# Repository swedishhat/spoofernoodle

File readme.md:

This board is designed to act as an ISO7816 smart card emulator
as well as a pass-through for the card.

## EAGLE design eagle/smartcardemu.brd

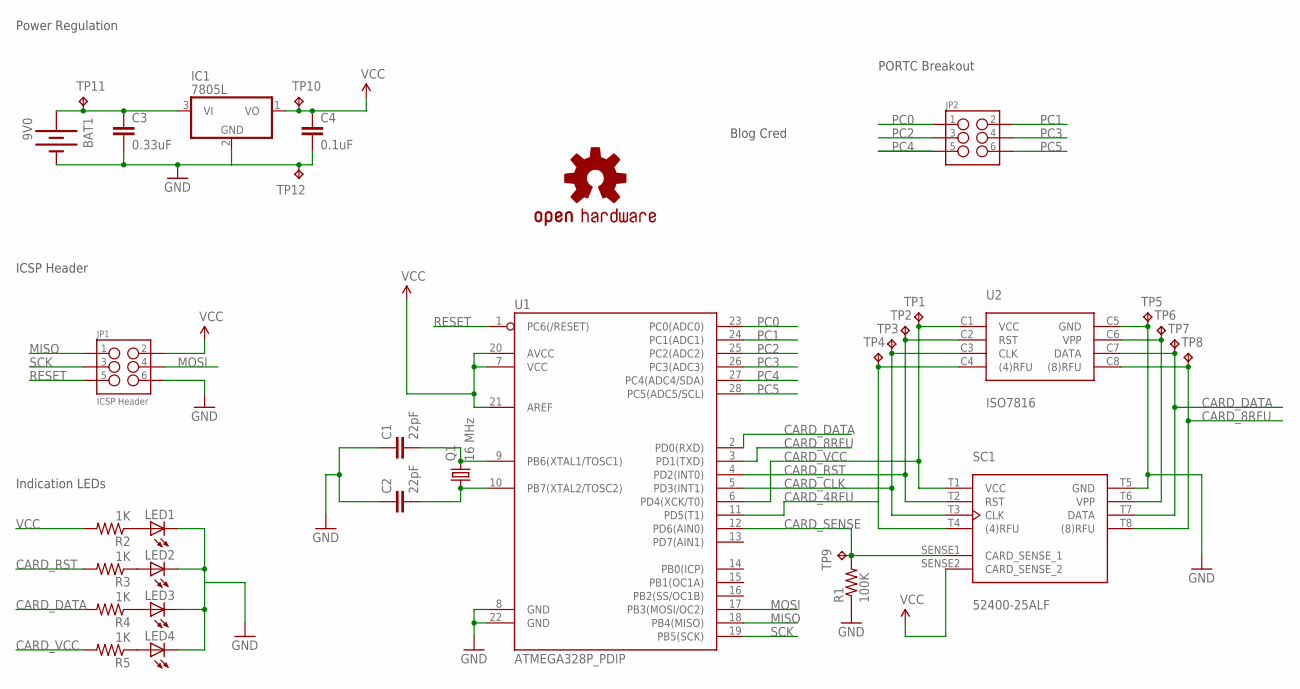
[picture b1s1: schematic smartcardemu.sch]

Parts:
BAT1: 9V0; BATTCON_9V
C1, C2: 22pF; CAP-PTH-SMALL
C3: 0.33uF; CAP-PTH-SMALL
C4: 0.1uF; CAP-PTH-SMALL
IC1: 7805L; TO92
JP1: ICSP Header; 2X3-NS
JP2: M03X2POGO_PINS; 2X3_POGO
LED1, LED2, LED3, LED4: LED5MM
LOGO1: OSHW-LOGOS; OSHW-LOGO-S
Q1: 16 MHz; HC49/S
R1: 100K; 0805-THM
R2, R3, R4, R5: 1K; 0805-THM
SC1: 52400-25ALF
TP1, TP2, TP3, TP4, TP5, TP6, TP7, TP8, TP9, TP10, TP11, TP12: TPPAD1-20; P1-20
U1: ATMEGA328P_PDIP; DIL28-3
U2: ISO7816; ISO7816-2

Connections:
CARD_4RFU: SC1.T4 ((4)RFU), TP4.TP, U1.11 (PD5(T1)), U2.C4 ((4)RFU)
CARD_8RFU: SC1.T8 ((8)RFU), TP8.TP, U1.3 (PD1(TXD)), U2.C8 ((8)RFU)
CARD_CLK: SC1.T3 (CLK), TP3.TP, U1.5 (PD3(INT1)), U2.C3 (CLK)
CARD_DATA: R4.2, SC1.T7 (DATA), TP7.TP, U1.2 (PD0(RXD)), U2.C7 (DATA)
CARD_RST: R3.2, SC1.T2 (RST), TP2.TP, U1.4 (PD2(INT0)), U2.C2 (RST)
CARD_SENSE: R1.2, SC1.SENSE1 (CARD_SENSE_1), TP9.TP, U1.12 (PD6(AIN0))
CARD_VCC: R5.2, SC1.T1 (VCC), TP1.TP, U1.6 (PD4(XCK/T0)), U2.C1 (VCC)
GND: BAT1.-, C1.1, C2.1, C3.2, C4.2, IC1.2 (GND), JP1.6, LED1.K (C), LED2.K (C), LED3.K (C), LED4.K (C), R1.1, SC1.T5 (GND), TP5.TP, TP12.TP, U1.8 (GND), U1.22 (GND), U2.C5 (GND)
MISO: JP1.1, U1.18 (PB4(MISO))
MOSI: JP1.4, U1.17 (PB3(MOSI/OC2))
unnamed: C1.2, Q1.2, U1.9 (PB6(XTAL1/TOSC1))
unnamed: C2.2, Q1.1, U1.10 (PB7(XTAL2/TOSC2))
unnamed: LED1.A, R2.1
unnamed: BAT1.+, C3.1, IC1.3 (VI), TP11.TP
unnamed: LED2.A, R3.1
unnamed: LED3.A, R4.1
unnamed: LED4.A, R5.1
unnamed: SC1.T6 (VPP), TP6.TP, U2.C6 (VPP)
PC0: JP2.P$1 (1)
RESET: JP1.5, U1.1 (PC6(/RESET))
SCK: JP1.3, U1.19 (PB5(SCK))
VCC: C4.1, IC1.1 (VO), JP1.2, R2.2, SC1.SENSE2 (CARD_SENSE_2), TP10.TP, U1.7 (VCC), U1.20 (AVCC), U1.21 (AREF)

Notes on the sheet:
Power Regulation
ICSP Header
Indication LEDs
Blog Cred
PORTC Breakout

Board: 2 copper layers, 34 parts (0 on the bottom side), 21 nets, no tracks yet.

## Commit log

2013-11-06 adding eagle and arduino files

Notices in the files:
parts and their libraries:
SparkFun-DigitalIC: Licensing: CC v3.0 Share-Alike You are welcome to use this library for commercial purposes.
